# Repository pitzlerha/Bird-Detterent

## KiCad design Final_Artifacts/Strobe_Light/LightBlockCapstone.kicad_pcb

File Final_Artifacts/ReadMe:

This folder contains all of the documentation on our Final Prototype.
For more information on the project, see our Project Document at https://docs.google.com/document/d/1QbJoJ92n-SqTIG3ZBJ0aD22_XHnqZucQURwWdW5gSv0/edit?usp=sharing

To build the prototype, complete the following steps:
1. Order all four PCBs. The design zip files can be found in PCB_Files. We recommend submitting these files to a board manufacturer such as OSH Park for manufacturing.
2. Order all relevant components. The components needed for each board can be found in BOM files located in PCB_Files. Alternatively you can consult the Master BOM in this folder.
3. Order the ESP32-S2-DevKitM-1R and Open MV Cam H7 Plus.
4. Follow the Instructions in the Microcontroller Code and Open MV Cam subfolders to flash the appropriate binaries onto the microcontrollers.
4. Use a 3D Printer to print the enclosure Pieces.
5. Follow the instructions in the Enclosure sub-folder to assemble the enclosure
6. Follow the board assembly notes contained in the ReadMes for each board. (Located as subfolders of this folder)
7. Directly connect the motion detector and ESP32 Dev board to the Control Board. (Male to female pin Header Connections).
8. Mount all of the Boards as directed in teh assembly notes contained in the Enclosure sub-folder.
9. Use Jumper pins to connect the boards as follows:

Power Supply 3.3V: -> 3.3V input of Control Board PCB
Power Supply GND: -> 3.3V ground input of Control Board PCB
Power Supply 5V (1): -> 5V input of Control Board PCB
Power Supply GND (1): -> 5V ground input of Control PCB
Power Supply 5V (2): -> 5V input of OpenMV Cam
Power Supply GND (2): -> 5V ground input of OpenMV Cam
Power Supply 5V Strobe: -> 5V input of Strobe Light PCB
Power Supply GND: -> 5V ground input of Strobe Light PCB
Control Board Strobe (bottom right): -> Gate signal input of Strobe Light PCB
Control Board Audio2 (Top Right): -> Input signal for Speaker
Control Board Audio G (Top Right): -> Ground for Speaker
Control Board SCL (Top Left of Center): -> I2C SCL pin of OpenMV Cam
Control Board SDA (Top Left of Center): -> I2C SDA pin of OpenMV Cam

Follow instructions in the Enclosure sub-folder to Weather Proof the Enclosure.

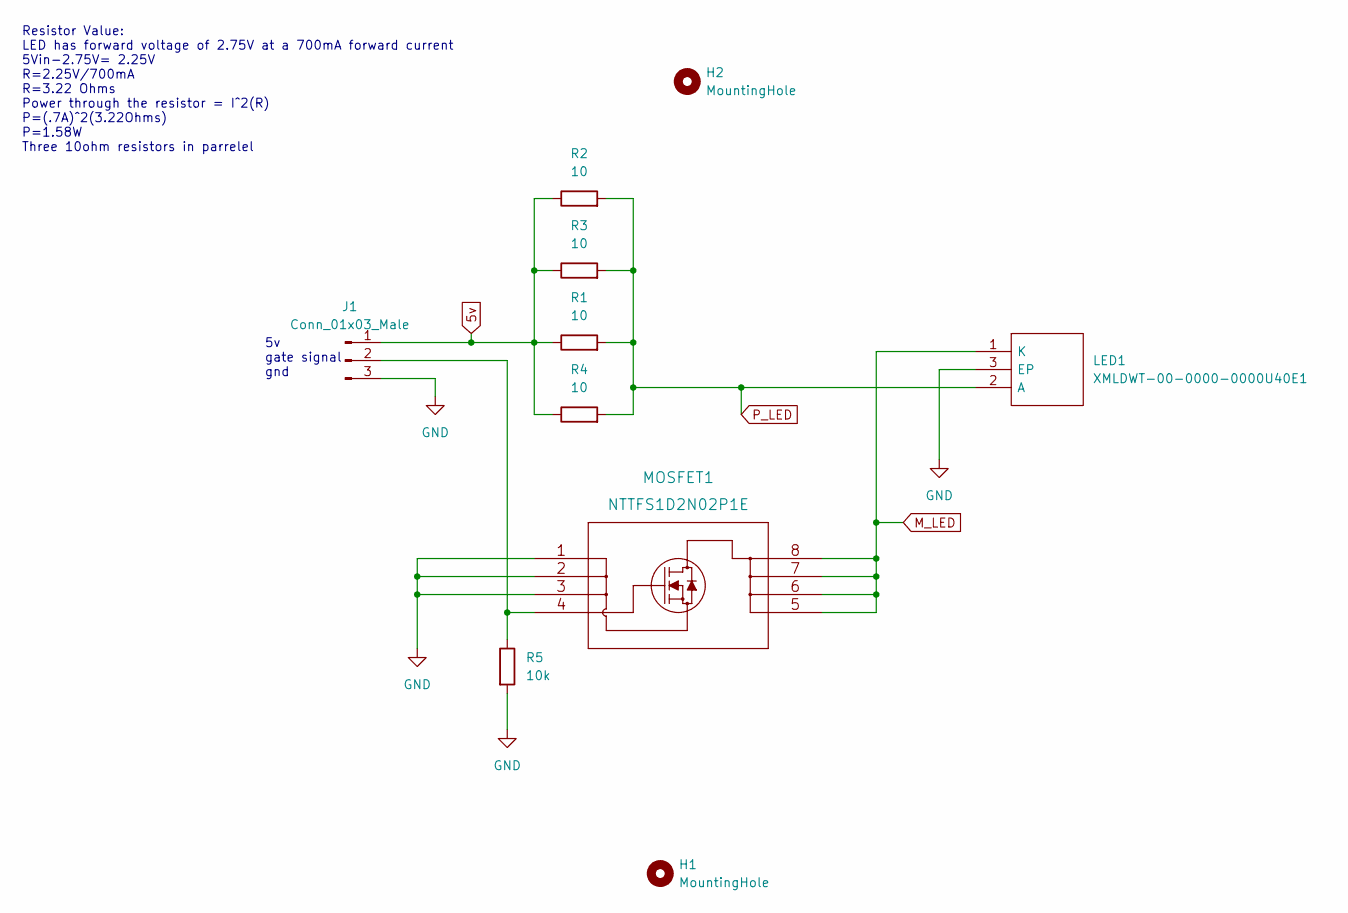
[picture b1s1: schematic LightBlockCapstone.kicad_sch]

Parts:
H1, H2: MountingHole; MountingHole_3.2mm_M3
J1: Conn_01x03_Male; PinHeader_1x03_P2.54mm_Vertical
LED1: XMLDWT-00-0000-0000U40E1; XMLDWT0000000000U40E1; Manufacturer_Part_Number XMLDWT-00-0000-0000U40E1; Mouser Part Number 941-XMLDWT0000U40E1
MOSFET1: NTTFS1D2N02P1E
R1, R2, R3, R4: 10; R_1206_3216Metric_Pad1.30x1.75mm_HandSolder
R5: 10k; R_1206_3216Metric_Pad1.30x1.75mm_HandSolder

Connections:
5v: J1.1, R1.1, R2.1, R3.1, R4.1
GND: J1.3, LED1.3 (EP), MOSFET1.1, MOSFET1.2, MOSFET1.3, R5.2
M_LED: LED1.1 (K), MOSFET1.5, MOSFET1.6, MOSFET1.7, MOSFET1.8
unnamed: J1.2, MOSFET1.4, R5.1
P_LED: LED1.2 (A), R1.2, R2.2, R3.2, R4.2

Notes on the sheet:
5v gate signal gnd
Resistor Value: LED has forward voltage of 2.75V at a 700mA forward current 5Vin-2.75V= 2.25V R=2.25V/700mA R=3.22 Ohms Power through the resistor = I^2(R) P=(.7A)^2(3.22Ohms) P=1.58W Three 10ohm resistors in parrelel

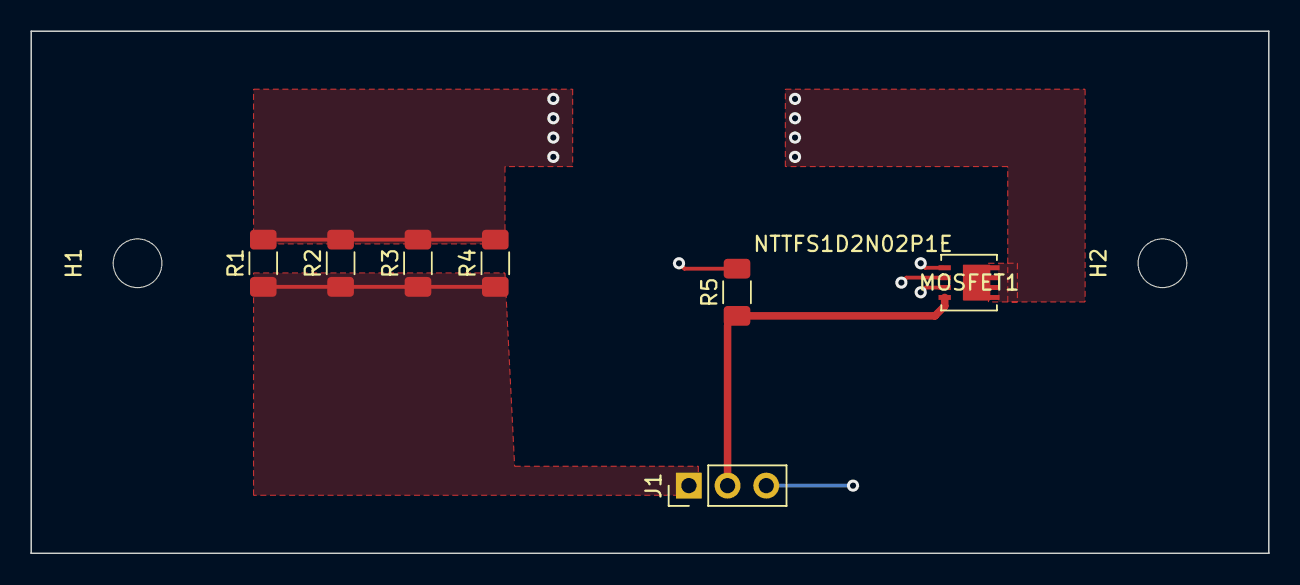
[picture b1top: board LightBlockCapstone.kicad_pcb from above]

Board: 2 copper layers, 81.3 x 34.3 mm, 10 parts (1 on the bottom side), 5 nets.

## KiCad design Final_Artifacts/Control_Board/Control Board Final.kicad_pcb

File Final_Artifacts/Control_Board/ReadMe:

To build the Control Board complete the following steps:

1. Submit the Control Board Final PCB v2.zip to a board manufacturer of your choice. We used https://oshpark.com/ to fabricate ours.
2. Order the Components listed in Control Board BOM.xlsx
3. Apply solder paste to all smd pads.
4. Carefully place smd components on their pads according to the BOM, schematic, and pcb layout.
5. Use a hot air gun to solder all smd components.
6. Check for and remove solder bridges.
7. Using a Soldering Iron and solder, solder all through hole components.

The Power Supply PCB has the following connections:
3V3 (bottom right): -> 3.3V output of Power Supply PCB
G (bottom right): -> 3.3V Ground output of Power Supply PCB
Strobe (bottom right): -> Gate signal input of Strobe Light PCB
Audio2 (Top Right): -> Input signal for Speaker
Audio G (Top Right): -> Ground for Speaker
5V (Top Middle): -> 5V output of Power Supply PCB
G (Top Middle): -> 5V Ground output of Power Supply PCB
SCL (Top Left of Center): -> I2C SCL pin of OpenMV Cam
SDA (Top Left of Center): -> I2C SDA pin of OpenMV Cam

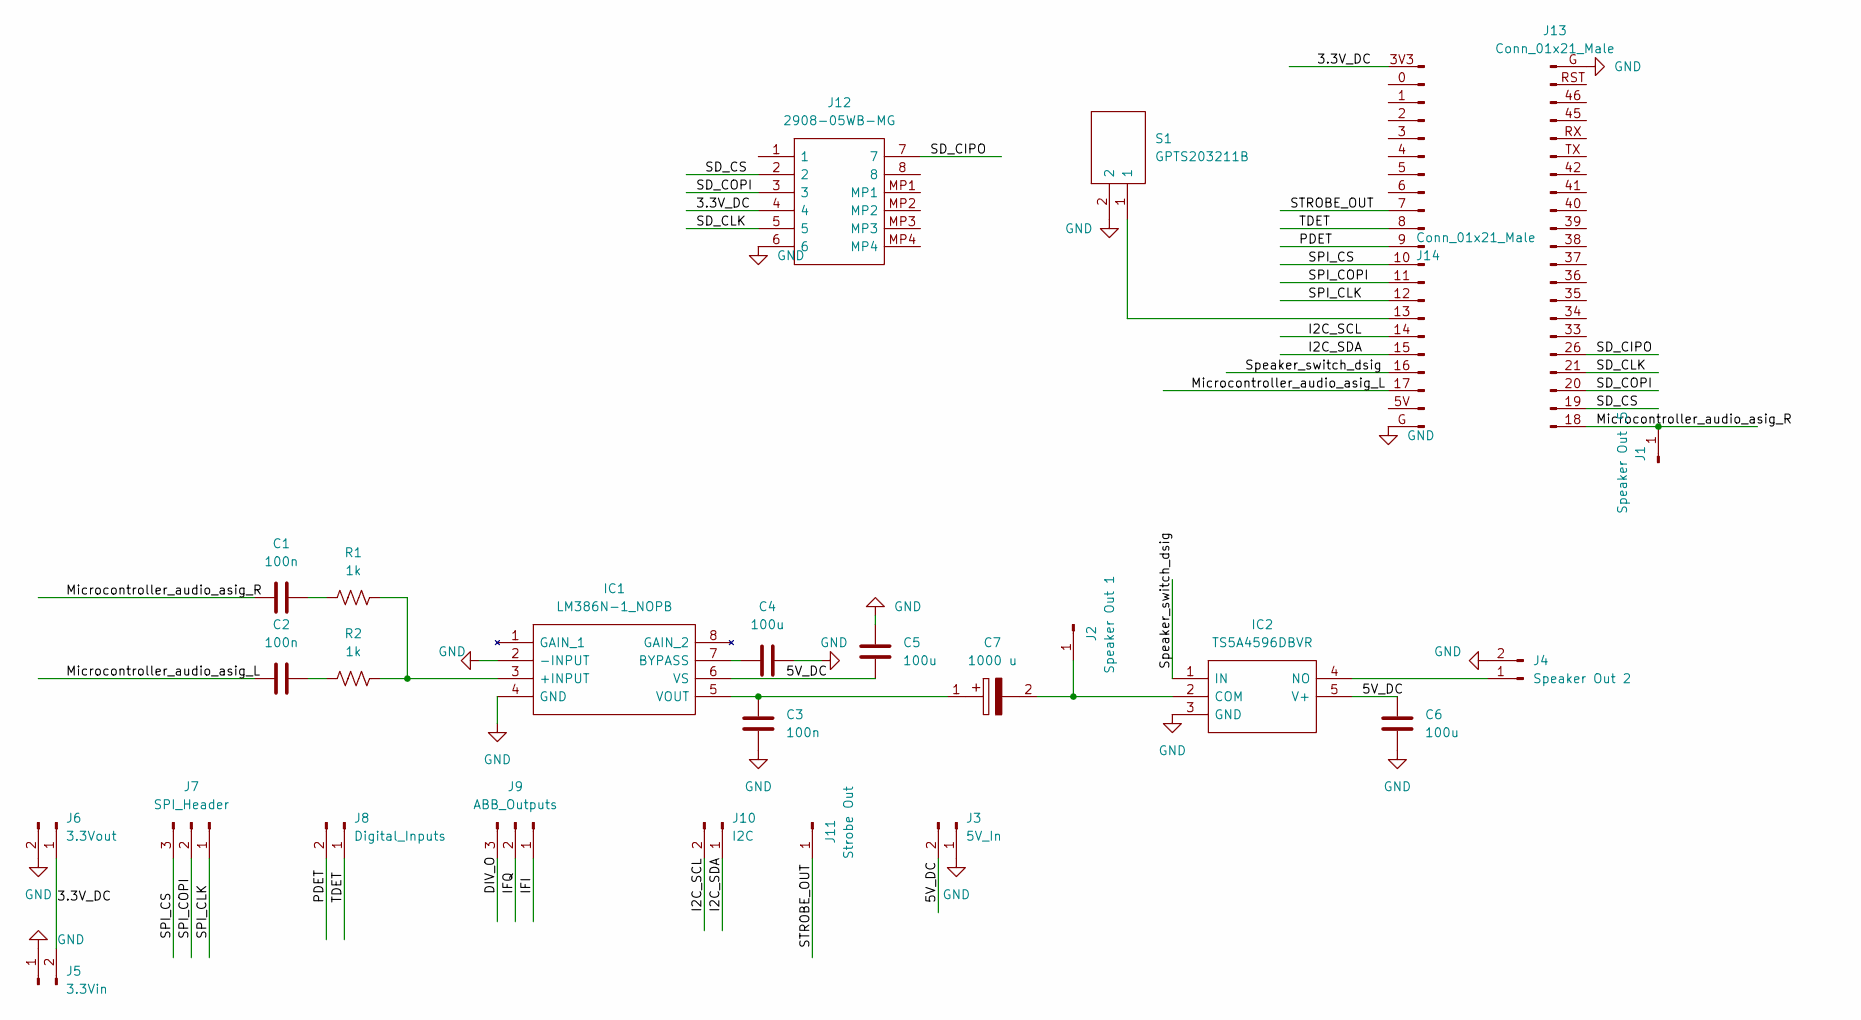
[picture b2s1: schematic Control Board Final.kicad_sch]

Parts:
C1, C2, C3: 100n; C_0805_2012Metric_Pad1.18x1.45mm_HandSolder
C4, C5, C6: 100u; C_1206_3216Metric_Pad1.33x1.80mm_HandSolder
C7: 1000 u; CAPAE1030X1050N; Mouser Part Number 710-865080257014
IC1: LM386N-1_NOPB; DIP794W53P254L959H508Q8N; Mouser Part Number 926-LM386N-1/NOPB
IC2: TS5A4596DBVR; SOT95P280X145-5N; Mouser Part Number 595-TS5A4596DBVR
J1: Speaker Out .5; PinHeader_1x01_P2.54mm_Vertical
J2: Speaker Out 1; PinHeader_1x01_P2.54mm_Vertical
J3: 5V_In; PinSocket_1x02_P2.54mm_Vertical
J4: Speaker Out 2; PinSocket_1x02_P2.54mm_Vertical
J5: 3.3Vin; PinSocket_1x02_P2.54mm_Vertical
J6: 3.3Vout; PinSocket_1x02_P2.54mm_Vertical
J7: SPI_Header; PinHeader_1x03_P2.54mm_Vertical
J8: Digital_Inputs; PinHeader_1x02_P2.54mm_Vertical
J9: ABB_Outputs; PinHeader_1x03_P2.54mm_Vertical
J10: I2C; PinHeader_1x02_P2.54mm_Vertical
J11: Strobe Out; PinHeader_1x01_P2.54mm_Vertical
J12: 2908-05WB-MG; 290805WBMG; Mouser Part Number 517-2908-05WB-MG
J13, J14: Conn_01x21_Male; PinHeader_1x21_P2.54mm_Vertical
R1, R2: 1k; R_0805_2012Metric_Pad1.20x1.40mm_HandSolder
S1: GPTS203211B; Mouser Part Number 629-GPTS203211B

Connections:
/3.3V_DC: J5.2, J6.1, J12.4, J14.3V3 (Pin_21)
/5V_DC: C5.2, C6.1, IC1.6 (VS), IC2.5 (V+), J3.2
/DIV_O: J9.3
/I2C_SCL: J10.2, J14.14 (Pin_6)
/I2C_SDA: J10.1, J14.15 (Pin_5)
/IFI: J9.1
/IFQ: J9.2
/Microcontroller_audio_asig_L: C2.1, J14.17 (Pin_3)
/Microcontroller_audio_asig_R: C1.1, J1.1, J13.18 (Pin_21)
/PDET: J8.2, J14.9 (Pin_11)
/SD_CIPO: J12.7, J13.26 (Pin_17)
/SD_CLK: J12.5, J13.21 (Pin_18)
/SD_COPI: J12.3, J13.20 (Pin_19)
/SD_CS: J12.2, J13.19 (Pin_20)
/SPI_CLK: J7.1, J14.12 (Pin_8)
/SPI_COPI: J7.2, J14.11 (Pin_9)
/SPI_CS: J7.3, J14.10
/STROBE_OUT: J11.1, J14.7 (Pin_13)
/Speaker_switch_dsig: IC2.1 (IN), J14.16 (Pin_4)
/TDET: J8.1, J14.8 (Pin_12)
GND: C3.1, C4.2, C5.1, C6.2, IC1.2 (-INPUT), IC1.4 (GND), IC2.3 (GND), J3.1, J4.2, J5.1, J6.2, J12.6, J13.G (Pin_1), J14.G (Pin_1), S1.2
unnamed: C1.2, R1.2
unnamed: C2.2, R2.2
unnamed: C3.2, C7.1, IC1.5 (VOUT)
unnamed: C4.1, IC1.7 (BYPASS)
unnamed: C7.2, IC2.2 (COM), J2.1
unnamed: IC1.3 (+INPUT), R1.1, R2.1
unnamed: IC2.4 (NO), J4.1
unnamed: J14.13 (Pin_7), S1.1

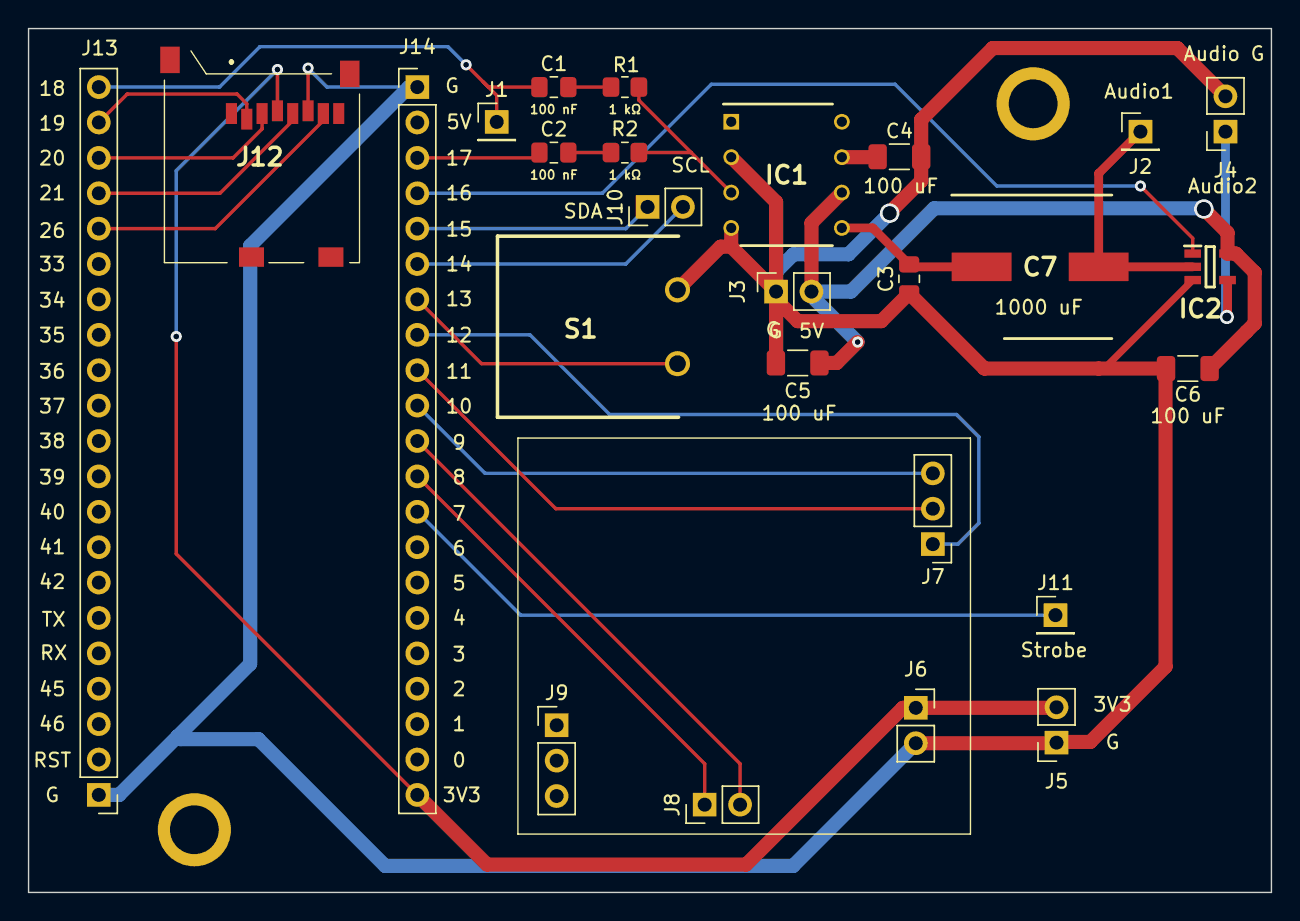
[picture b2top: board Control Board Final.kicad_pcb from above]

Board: 2 copper layers, 89.2 x 62.0 mm, 26 parts (0 on the bottom side), 26 nets.

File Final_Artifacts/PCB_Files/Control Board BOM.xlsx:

Control PCB BOM
Part Number | Manufacturer | Source | Part Name | Identifier | Quantity | Price per Unit | Total Cost ($) | Link
LM386N-1/NOPB | Texas Instruments | Mouser | Audio Amplifier | IC1 | 1 | 1.34 | 1.34 | https://www.mouser.com/ProductDetail/Texas-Instruments/LM386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
TS5A4596DBVR | Texas Instruments | Mouser | Analog Switch | IC2 | 1 | 0.5 | 0.5 | https://www.mouser.com/ProductDetail/Texas-Instruments/TS5A4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
885012207072 | Wurth Elektronik | Mouser | .1 uF Ceramic Capacitor | C1, C2, C3 | 3 | 0.1 | 0.30000000000000004 | https://www.mouser.com/ProductDetail/Wurth-Elektronik/885012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
GRM31CR61A107MEA8L | Murata Electonics | Mouser | 100 uF Ceramic Capacitor | C4, C5, C6 | 3 | 0.47 | 1.41 | https://www.mouser.com/ProductDetail/Murata-Electronics/GRM3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
865080257014 | Wurth Elektronik | Mouser | 1000 uF Electolytic Capacitor | C7 | 1 | 0.99 | 0.99 | https://www.mouser.com/ProductDetail/Wurth-Elektronik/865080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
WCR0805-1K0FI | Welwyn Components / TT Electronics | Mouser | 1 kΩ Resistor | R1, R2 | 2 | 0.1 | 0.2 | https://www.mouser.com/ProductDetail/Welwyn-Components-TT-El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
GPTS203211B | CW Industries | Mouser | Pushbutton Switch | S1 | 1 | 1.67 | 1.67 | https://www.mouser.com/ProductDetail/CW-Industries/GPTS20321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
2908-05WB-MG | 3M | Mouser | SD Card Module | J12 | 0 | 4.8099999999999996 | 0 | https://www.mouser.com/ProductDetail/3M-Electronic-Solutions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
P106-1418689519 | Jameco ValuePro | Tekbots | 1 in header pins | J3, J4, J5, J10, J11 | 8 | 0.03 | 0.24 | https://secure.touchnet.net/C20159_ustores/web/product_detai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
15Fx1-254mm | Gravitech | Mouser | 1 in header female conn | J6, J7, J8, J9, J13, J14 | 52 | 7.0000000000000007E-2 | 3.6400000000000006 | https://www.mouser.com/ProductDetail/Gravitech/15Fx1-254mm?q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
 | OSH Park | OSH Park | PCB |  | 1 | 14.27 | 14.27 | https://oshpark.com/
 |  |  |  |  |  | Total: | 24.560000000000002

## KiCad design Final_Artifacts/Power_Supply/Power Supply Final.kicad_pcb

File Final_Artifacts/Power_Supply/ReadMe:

To build the Power Supply Board complete the following steps:

1. Submit the Power Supply Final PCB files.zip to a board manufacturer of your choice. We used https://oshpark.com/ to fabricate ours.
2. Order the Components listed in Power Supply Final BOM.xlsx
3. Apply solder paste to all smd pads.
4. Carefully place smd components on their pads according to the BOM, schematic, and pcb layout.
5. Use a hot air gun to solder all smd components.
6. Check for solder bridges, especially on the switching voltage regulator and current limiting switch ICs.
7. Use a DMM to verify that there is no short between any of the outputs and ground.
8. Using a Soldering Iron and solder, solder all through hole components.
9. MAKE SURE THE TRANSFORMER DOT IS FACING THE SUPERCAPACITORS AND ICS. (the dot denotes the secondary side, the primary side should be connected to wall power)
10. Be careful when applying wall power to circuitry for the first time.

The Power Supply PCB has the following connections:
3.3V (Right Center): -> 3.3V input of Control Board PCB
GND (Right Center): -> 3.3V ground input of Control Board PCB
5V (1) (Bottom Right): -> 5V input of Control Board PCB
GND (1) (Bottom Right): -> 5V ground input of Control PCB
5V (2) (Bottom Right): -> 5V input of OpenMV Cam
GND (2) (Bottom Right): -> 5V ground input of OpenMV Cam
5V Strobe (Top Right): -> 5V input of Strobe Light PCB
GND (Top Right): -> 5V ground input of Strobe Light PCB

Note: When power is initially applied, the supercapactors will take time to charge. Expect the 5V strobe output to rise to 5V slowly over the course of several minutes.
Note: The supercapacitors keep the outputs alive after wall power is disconnected. Circuitry will function until they are discharged.

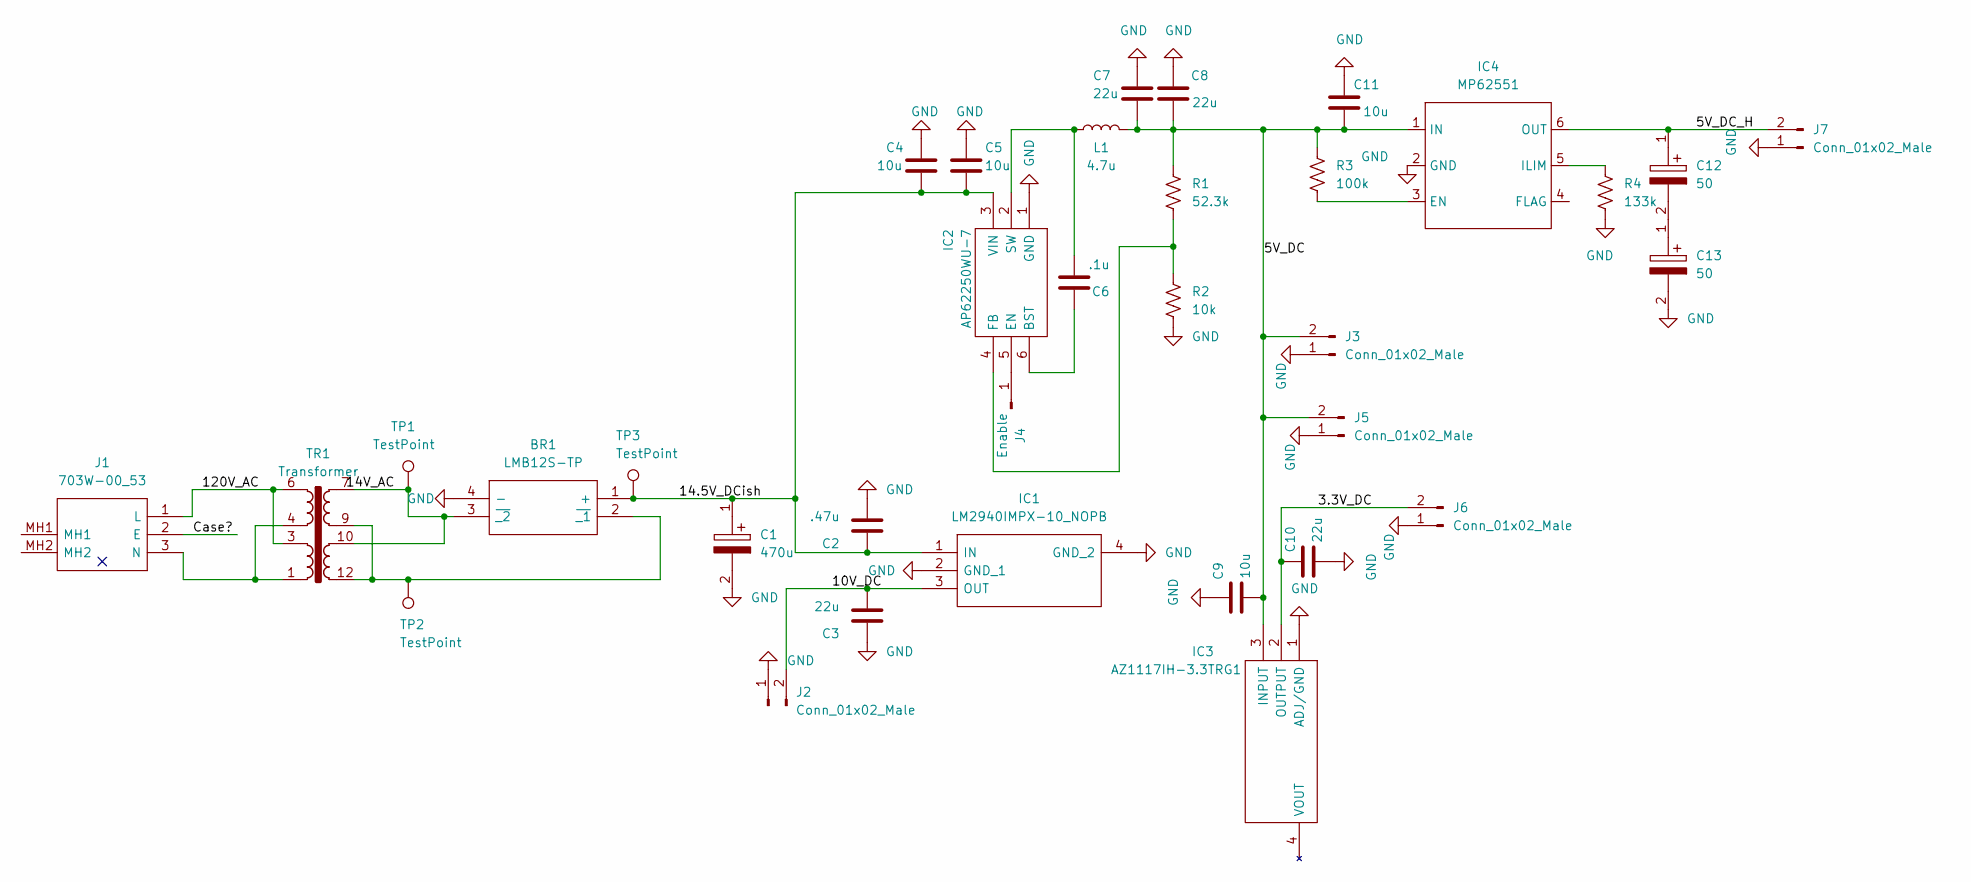
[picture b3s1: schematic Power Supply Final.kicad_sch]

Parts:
BR1: LMB12S-TP; LMB12STP; Mouser Part Number 833-LMB12S-TP
C1: 470u; CAPAE830X1050N; Mouser Part Number 661-EMZL250ARA471MHA
C2: .47u; C_0805_2012Metric_Pad1.18x1.45mm_HandSolder
C3, C7, C8, C10: 22u; C_0805_2012Metric_Pad1.18x1.45mm_HandSolder
C4, C5, C9, C11: 10u; C_0805_2012Metric_Pad1.18x1.45mm_HandSolder
C6: .1u; C_0805_2012Metric_Pad1.18x1.45mm_HandSolder
C12, C13: 50; CP_Radial_D18.0mm_P7.50mm
IC1: LM2940IMPX-10_NOPB; SOT230P700X180-4N; Mouser Part Number 926-LM2940IMPX10NOPB
IC2: AP62250WU-7; SOT95P280X100-6N; Mouser Part Number 621-AP62250WU-7
IC3: AZ1117IH-3.3TRG1; SOT230P700X180-4N; Mouser Part Number 621-AZ1117IH-3.3TRG1
IC4: MP62551; TSOT-23-6_HandSoldering
J1: 703W-00_53; 703W0053; Mouser Part Number 562-703W-00/53
J2, J3, J5, J6, J7: Conn_01x02_Male; PinHeader_1x02_P2.54mm_Vertical
J4: Enable; PinHeader_1x01_P2.54mm_Vertical
L1: 4.7u; PA5432.153NLT
R1: 52.3k; R_0805_2012Metric_Pad1.20x1.40mm_HandSolder
R2: 10k; R_0805_2012Metric_Pad1.20x1.40mm_HandSolder
R3: 100k; R_0805_2012Metric_Pad1.20x1.40mm_HandSolder
R4: 133k; R_0805_2012Metric_Pad1.20x1.40mm_HandSolder
TP1, TP2, TP3: TestPoint; TestPoint_Pad_2.5x2.5mm
TR1: Transformer; Transformer_20VAC

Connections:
/3.3V_DC: C10.2, IC3.2 (OUTPUT), J6.2
/5V_DC: C7.2, C8.1, C9.1, C11.1, IC3.3 (INPUT), IC4.1 (IN), J3.2, J5.2, L1.2, R1.1, R3.2
/5V_DC_H: C12.1, IC4.6 (OUT), J7.2
/10V_DC: C3.2, IC1.3 (OUT), J2.2
/14.5V_DCish: BR1.1 (+), C1.1, C2.1, C4.2, C5.2, IC1.1 (IN), IC2.3 (VIN), TP3.1
/120V_AC: J1.1 (L), TR1.3, TR1.6
/Case?: J1.2 (E)
GND: BR1.4 (-), C1.2, C2.2, C3.1, C4.1, C5.1, C7.1, C8.2, C9.2, C10.1, C11.2, C13.2, IC1.2 (GND_1), IC1.4 (GND_2), IC2.1 (GND), IC3.1 (ADJ/GND), IC4.2 (GND), J2.1, J3.1, J5.1, J6.1, J7.1, R2.2, R4.1
unnamed: BR1.2 (~_1), TP2.1, TR1.9, TR1.12
unnamed: BR1.3 (~_2), TP1.1, TR1.7, TR1.10
unnamed: C6.1, IC2.6 (BST)
unnamed: C6.2, IC2.2 (SW), L1.1
unnamed: C12.2, C13.1
unnamed: IC2.4 (FB), R1.2, R2.1
unnamed: IC2.5 (EN), J4.1
unnamed: IC4.3 (EN), R3.1
unnamed: IC4.5 (ILIM), R4.2
unnamed: J1.3 (N), TR1.1, TR1.4

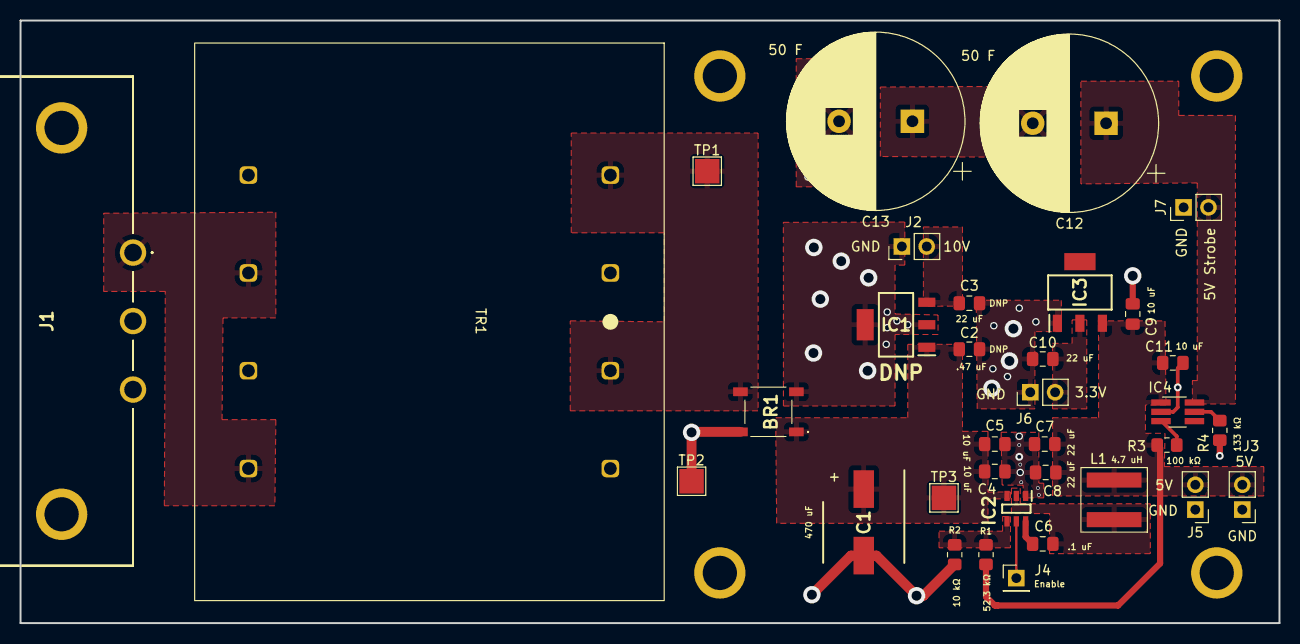
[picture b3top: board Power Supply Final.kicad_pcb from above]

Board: 2 copper layers, 128.7 x 61.6 mm, 34 parts (0 on the bottom side), 17 nets.

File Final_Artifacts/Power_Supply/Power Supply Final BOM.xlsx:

Power Supply v2 BOM
Part Number | Manufacturer | Source | Part Name | Identifier | Quantity | Price per Unit ($) | Total Cost ($) | Link
183H16 | Hammond Manufacturing | Mouser | 20VA 115:8 Stepdown Transformer | TR1 | 1 | 17.04 | 17.04 | https://www.mouser.com/ProductDetail/Hammond-Manufacturing/1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
LM2940IMPX-10/NOPB | Texas Instruments | Mouser | 10V 1A LDO Linear Voltage Regulator | IC1 | 1 | 1.99 | 1.99 | https://www.mouser.com/ProductDetail/Texas-Instruments/LM294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
AP62250WU-7 | Diodes Incorporated | Mouser | 5V 2.5A 1.3MHz Stepdown Switching Voltage Regulator | IC2 | 1 | 0.49 | 0.49 | https://www.mouser.com/ProductDetail/Diodes-Incorporated/AP6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
AZ1117IH-3.3TRG1 | Diodes Incorporated | Mouser | 3.3V 1.35A LDO Linear Voltage Regulator | IC3 | 1 | 0.4 | 0.4 | https://www.mouser.com/ProductDetail/Diodes-Incorporated/AZ1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
MP62551DJ-LF-P | Monolithic Power Systems | Mouser | Current Limit Switch | IC4 | 1 | 1.84 | 1.84 | https://www.mouser.com/ProductDetail/Monolithic-Power-System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
833-LMB14S-TP | Micro Commercial Components (MCC) | Mouser | Bridge Rectifier | BR1 | 1 | 0.48 | 0.48 | https://www.mouser.com/ProductDetail/Micro-Commercial-Compon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
PA5432.472NLT | Pulse Electronics | Mouser | 4.7 uH Inductor | L1 | 1 | 2.15 | 2.15 | https://www.mouser.com/ProductDetail/Pulse-Electronics/PA543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
EMZL250ARA471MHA0G | United Chemi-Con | Mouser | 470 uF Electrolytic Capacitor | C1 | 1 | 0.95 | 0.95 | https://www.mouser.com/ProductDetail/United-Chemi-Con/EMZL25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
CL21B474KAFNFNE | Samsung Electro-Mechanics | Mouser | .47 uF Ceramic Capacitor | C2 | 1 | 0.1 | 0.1 | https://www.mouser.com/ProductDetail/Samsung-Electro-Mechani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
CL21B104KBCNNNC | Samsung Electro-Mechanics | Mouser | .1 uF Ceramic Capacitor | C6 | 1 | 0.1 | 0.1 | https://www.mouser.com/ProductDetail/Samsung-Electro-Mechani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
CL21A106KAYNNNE | Samsung Electro-Mechanics | Mouser | 10 uF Ceramic Capacitor | C4, C5, C9, C11 | 4 | 0.16 | 0.64 | https://www.mouser.com/ProductDetail/Samsung-Electro-Mechani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
CL21A226MAYNNNE | Samsung Electro-Mechanics | Mouser | 22 uF Ceramic Capacitor | C3, C7, C8, C10 | 4 | 0.26 | 1.04 | https://www.mouser.com/ProductDetail/Samsung-Electro-Mechani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
MAL223551008E3 | Vishay / BC Components | Mouser | 50 F Supercapacitor | C12, C13 | 2 | 6.07 | 12.14 | https://www.mouser.com/ProductDetail/594-MAL223551008E3
ERJ-6ENF5232V | Panasonic | Mouser | 52.3 kΩ Resistor | R1 | 1 | 0.1 | 0.1 | https://www.mouser.com/ProductDetail/Panasonic/ERJ-6ENF5232V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
CR0805-FX-1002ELF | Bourns | Mouser | 10 kΩ Resistor | R2 | 1 | 0.1 | 0.1 | https://www.mouser.com/ProductDetail/Bourns/CR0805-FX-1002EL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
CRCW0805100KFKEBC | Vishay / Dale | Mouser | 100 kΩ Resistor | R3 | 1 | 0.1 | 0.1 | https://www.mouser.com/ProductDetail/Vishay-Dale/CRCW0805100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
RC0805FR-07133KL | YAGEO | Mouser | 133 kΩ Resistor | R4 | 1 | 0.1 | 0.1 | https://www.mouser.com/ProductDetail/YAGEO/RC0805FR-07133KL?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
703W-00/53 | Qualtek | Mouser | IEC-320 PCB Connector | J1 | 1 | 1.76 | 1.76 | https://www.mouser.com/ProductDetail/Qualtek/703W-00-53?qs=%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
P106-1418689519 | Jameco ValuePro | Tekbots | 1 in header pins | J2 - J7 | 11 | 0.03 | 0.32999999999999996 | https://secure.touchnet.net/C20159_ustores/web/product_detai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
 | OSH Park | OSH Park | Custom PCB 1 |  | 1 | 20.5 | 20.5 | https://oshpark.com/
 |  |  |  |  |  | Total: | 62.35

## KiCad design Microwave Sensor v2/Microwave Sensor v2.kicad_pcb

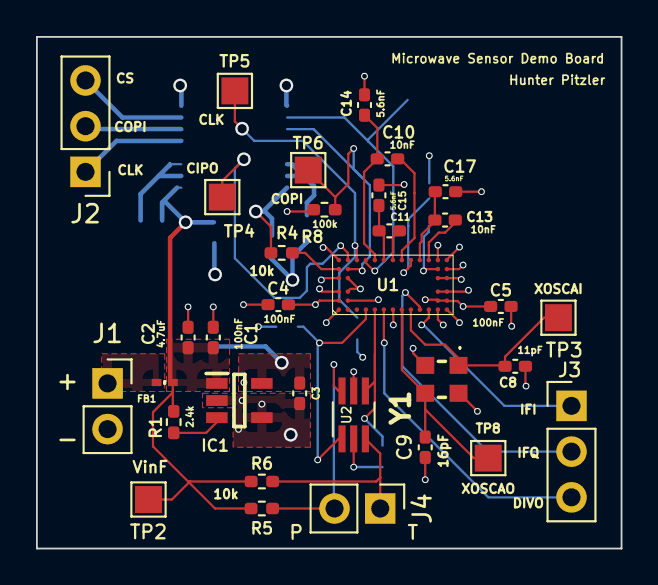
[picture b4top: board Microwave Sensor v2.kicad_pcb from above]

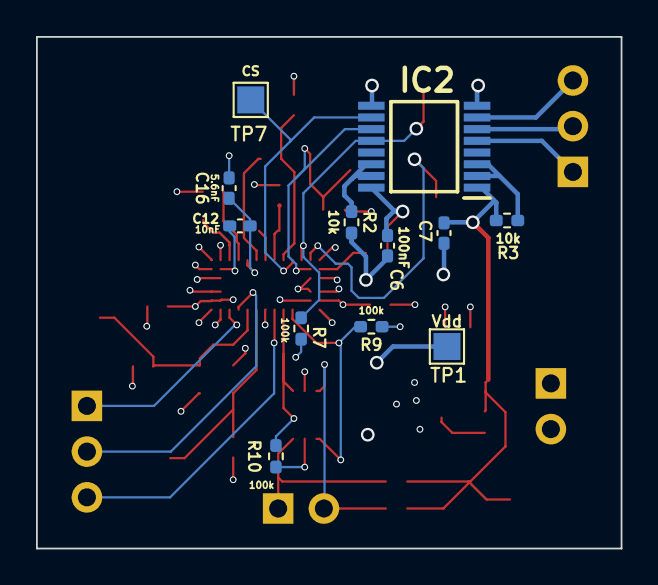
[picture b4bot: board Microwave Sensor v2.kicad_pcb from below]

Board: 4 copper layers, 32.5 x 28.4 mm, 45 parts (12 on the bottom side), 32 nets.

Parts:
C1, C4, C5, C6, C7: 100n; C_0402_1005Metric_Pad0.74x0.62mm_HandSolder
C2, C3: 4.7u; C_0402_1005Metric_Pad0.74x0.62mm_HandSolder
C8: 11p; C_0402_1005Metric_Pad0.74x0.62mm_HandSolder
C9: 16p; C_0402_1005Metric_Pad0.74x0.62mm_HandSolder
C10, C11, C12, C13: 10n; C_0402_1005Metric_Pad0.74x0.62mm_HandSolder
C14, C15, C16, C17: 5.6n; C_0402_1005Metric_Pad0.74x0.62mm_HandSolder
FB1: MMZ0603S121HT000; BEADC0603X33N
IC1: TPS7A2015PDBVR; SOT95P280X145-5N
IC2: SN74AVC4T245PWR; SOP65P640X120-16N
J1: 3.3Vin; PinSocket_1x02_P2.54mm_Vertical
J2: SPI_Header; PinHeader_1x03_P2.54mm_Vertical
J3: ABB_Outputs; PinHeader_1x03_P2.54mm_Vertical
J4: Digital_Outputs; PinHeader_1x02_P2.54mm_Vertical
R1: 2.4k; R_0402_1005Metric_Pad0.72x0.64mm_HandSolder
R2, R3, R4, R5, R6: 10k; R_0402_1005Metric_Pad0.72x0.64mm_HandSolder
R7, R8, R9, R10: 100k; R_0402_1005Metric_Pad0.72x0.64mm_HandSolder
TP1, TP2, TP3, TP4, TP5, TP6, TP7, TP8: TestPoint; TestPoint_Pad_1.5x1.5mm
U1: BGT60LTR11AIPE6327XUMA2; BGT60LTR11AIPE6327XUMA2 v2
U2: Level_Shifter; SOT-363_SC-70-6_Handsoldering
Y1: FH3840024Z

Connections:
/IFIAI: C10.2, U1.H6 (IFIAI)
/IFIAIX: C11.2, U1.G6 (IFIAIX)
/IFQAI: C12.2, U1.M5 (IFQAI)
/IFQAIX: C13.2, U1.L6 (IFQAIX)
/Vdd: C3.1, C4.2, C5.1, C6.2, IC1.5 (OUT), IC2.16 (VCCB), R4.1, R9.1, R10.2, TP1.1, U1.A2 (VDD_RF), U1.B2 (VDD_RF), U1.M2 (VDD_PLL), U1.M6 (QS1), U1.N2 (VDD_PLL), U2.2 (Ref1), U2.5 (Ref2)
/VinF: C1.2, C2.2, C7.1, FB1.2, IC1.1 (IN), IC2.1 (VCCA), R1.1, R3.1, R5.2, R6.2, TP2.1
GND: C1.1, C2.1, C3.2, C4.1, C5.2, C6.1, C7.2, C8.2, C9.1, C14.2, C15.2, C16.2, C17.2, IC1.2 (GND), IC1.4 (N/C), IC2.8 (GND_1), IC2.9 (GND_2), J1.2, R2.2, R7.1, R8.2, U1.A1 (GND), U1.A3 (GND), U1.A4 (GND), U1.A6 (GND), U1.B3 (GND), U1.B4 (GND), U1.G1 (PLL_TRIG), U1.M1 (QS4), U1.M3 (GND), U1.M4 (GND), U1.N1 (GND), U1.N3 (GND), U1.N4 (GND), U1.N5 (QS2), U1.N6 (GND), Y1.2 (CASE_1), Y1.4 (CASE_2)
unnamed: C8.1, TP3.1, U1.J1 (XOSC_AI), Y1.1 (XTAL_1)
unnamed: C9.2, TP8.1, U1.H1 (XOSC_AO), Y1.3 (XTAL_2)
unnamed: C10.1, C14.1, U1.E6 (IFIAO)
unnamed: C11.1, C15.1, U1.F6 (IFIAOX)
unnamed: C12.1, C16.1, U1.J6 (IFQAO)
unnamed: C13.1, C17.1, U1.K6 (IFQAOX)
unnamed: FB1.1, J1.1
unnamed: IC1.3 (EN), R1.2
unnamed: IC2.2 (1DIR), IC2.3 (2DIR), R3.2
unnamed: IC2.5 (1A2), J2.1
unnamed: IC2.6 (2A1), J2.2
unnamed: IC2.7 (2A2), J2.3
unnamed: IC2.10 (2B2), TP7.1, U1.D6 (SPICS)
unnamed: IC2.11 (2B1), R8.1, TP6.1, U1.B5 (SPIDI)
unnamed: IC2.12 (1B2), R7.2, TP5.1, U1.C6 (SPICLK)
unnamed: IC2.14 (2~OE), IC2.15 (1~OE), R2.1
unnamed: J3.1, U1.L1 (IFI)
unnamed: J3.2, U1.K1 (IFQ)
unnamed: J3.3, U1.F1 (DIV_O)
unnamed: J4.1, R6.1, U2.3 (Out2)
unnamed: J4.2, R5.1, U2.6 (Out1)
unnamed: R4.2, U1.A5 (SPIRST_N)
unnamed: R9.2, U1.D1 (PDET), U2.1 (In1)
unnamed: R10.1, U1.E1 (TDET), U2.4 (In2)
unnamed: TP4.1, U1.B6 (SPIDO)

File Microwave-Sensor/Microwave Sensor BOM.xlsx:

Microwave Sensor BOM
Part Number | Manufacturer | Source | Part Name | Identifier | Quantity | Price per Unit ($) | Total Cost ($) | Link
BGT60LTR11AIPE6327XUMA2 | Infineon | Mouser | Microwave Sensor | U1 | 1 | 12.5 | 12.5 | https://www.mouser.com/ProductDetail/Infineon-Technologies/B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
BSD840N H6327 | Infineon | Mouser | Level Shifter | U2 | 1 | 0.42 | 0.42 | https://www.mouser.com/ProductDetail/Infineon-Technologies/B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
FH3840024Z | Diodes Incorporated | Mouser | 38.4 MHz Crystal | Y1 | 1 | 0.96 | 0.96 | https://www.mouser.com/ProductDetail/Diodes-Incorporated/FH3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
TPS7A2015PDBVR | Texas Instruments | Mouser | LDO Voltage Regulator | IC1 | 1 | 0.49 | 0.49 | https://www.mouser.com/ProductDetail/Texas-Instruments/TPS7A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
SN74AVC4T245PWR | Texas Instruments | Mouser | 4-Bit Level Shifter | IC2 | 1 | 1.45 | 1.45 | https://www.mouser.com/ProductDetail/Texas-Instruments/SN74A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
MMZ0603S121HT000 | TDK | Mouser | Ferrite Bead/Inductor | FB1 | 1 | 0.13 | 0.13 | https://www.mouser.com/ProductDetail/TDK/MMZ0603S121HT000?qs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
CL05B104JO5NNNC | Samsung Electro-Mechanics | Mouser | 100 nF Capacitor | C1, C4, C5, C6, C7 | 5 | 0.1 | 0.5 | https://www.mouser.com/ProductDetail/Samsung-Electro-Mechani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
GRM155R60J475ME47J | Murata | Mouser | 4.7 uF Capacitor | C2, C3 | 2 | 0.12 | 0.24 | https://www.mouser.com/ProductDetail/Murata-Electronics/GRM1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
C0402C110K5HACTU | KEMET | Mouser | 11 pF Capacitor | C8 | 1 | 0.1 | 0.1 | https://www.mouser.com/ProductDetail/KEMET/C0402C110K5HACTU?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
GCM1555C1H160FA16D | Murata | Mouser | 16 pF Capacitor | C9 | 1 | 0.1 | 0.1 | https://www.mouser.com/ProductDetail/Murata-Electronics/GCM1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
GRT155R71H103KE01D | Murata | Mouser | 10 nF Capacitor | C10, C11, C12, C13 | 4 | 0.1 | 0.4 | https://www.mouser.com/ProductDetail/Murata-Electronics/GRT1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
GRM15XR71C562KA86D | Murata | Mouser | 5.6 nF Capactior | C14, C15, C16, C17 | 4 | 0.1 | 0.4 | https://www.mouser.com/ProductDetail/Murata-Electronics/GRM1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
RR0510P-242-D | Susumu | Mouser | 2.4 kΩ Resistor | R1 | 1 | 0.12 | 0.12 | https://www.mouser.com/ProductDetail/Susumu/RR0510P-242-D?qs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
RT0402FRE1310KL | YAGEO | Mouser | 10 kΩ Resistor | R2, R3, R4, R5, R6 | 5 | 0.1 | 0.5 | https://www.mouser.com/ProductDetail/YAGEO/RT0402FRE1310KL?q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
CRT0402-FZ-1003GLF | Bourns | Mouser | 100 kΩ Resistor | R7, R8, R9, R10 | 4 | 0.11 | 0.44 | https://www.mouser.com/ProductDetail/Bourns/CRT0402-FZ-1003G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
 | OSH Park | OSH Park | PCB |  | 1 | 4.7699999999999996 | 4.7699999999999996 | https://oshpark.com/
 |  |  |  |  |  | Total: | 23.52

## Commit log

2023-02-02 Create Hi
2023-02-23 Create Power-Supply
2023-06-06 Add files via upload
    OpenMV Final Code
2023-06-06 Final OpenMV Camera Code
2023-06-09 Create no_birds_pictures
2023-06-09 Create temp

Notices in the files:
parts and their libraries:
Copyright 2021 Accelerated Designs. All rights reserved.
